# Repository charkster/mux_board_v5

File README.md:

# mux_board_v5
Custom PCB with SAMD21 QT PY controlling TWO ADG1606BRUZ 16 input muxes! This board is 30% smaller than V3 and uses a single 16x2 pin header. There are two firmwares for this board, as the backside input pin numbering does not match the topside numbering. You can select which side you would like to be on-top... the QT PY board is much taller than the ADG1606BRUZ packages, and I plan to have the backside on-top (to aviod any unwanted contact with the boards that I connect to).

Check-out my **PDF** [schematic](https://github.com/charkster/mux_board_v5/blob/main/mux_board_v5.pdf) !!

The SAMD21 QT PY can be programmed with the appropriate file (drag-n-drop) from the uf2_firmware folder. 

**Supported USBTMC commands:**

**MUX1:EN 1** # enable MUX1, a zero will disable the mux

**MUX1:SEL 1** # select S1 input, values 1 through 16 are valid

**MUX1:EN?** # this query returns the state of MUX1

**MUX1:SEL?** # this query returns the presently selected input

***RST** # disables all MUX enables

***IDN?** # returns valid commands and this URL

2x16 2.54mm stacking headers can be found on [Aliexpress](https://www.aliexpress.us/item/2255800630914427.html)

SAMD21 QT PY and ADG1606BRUZ ICs can be found on Digikey/Mouser.

The tinyusb_usbtmc_src files are modifications of https://github.com/hathach/tinyusb source files.

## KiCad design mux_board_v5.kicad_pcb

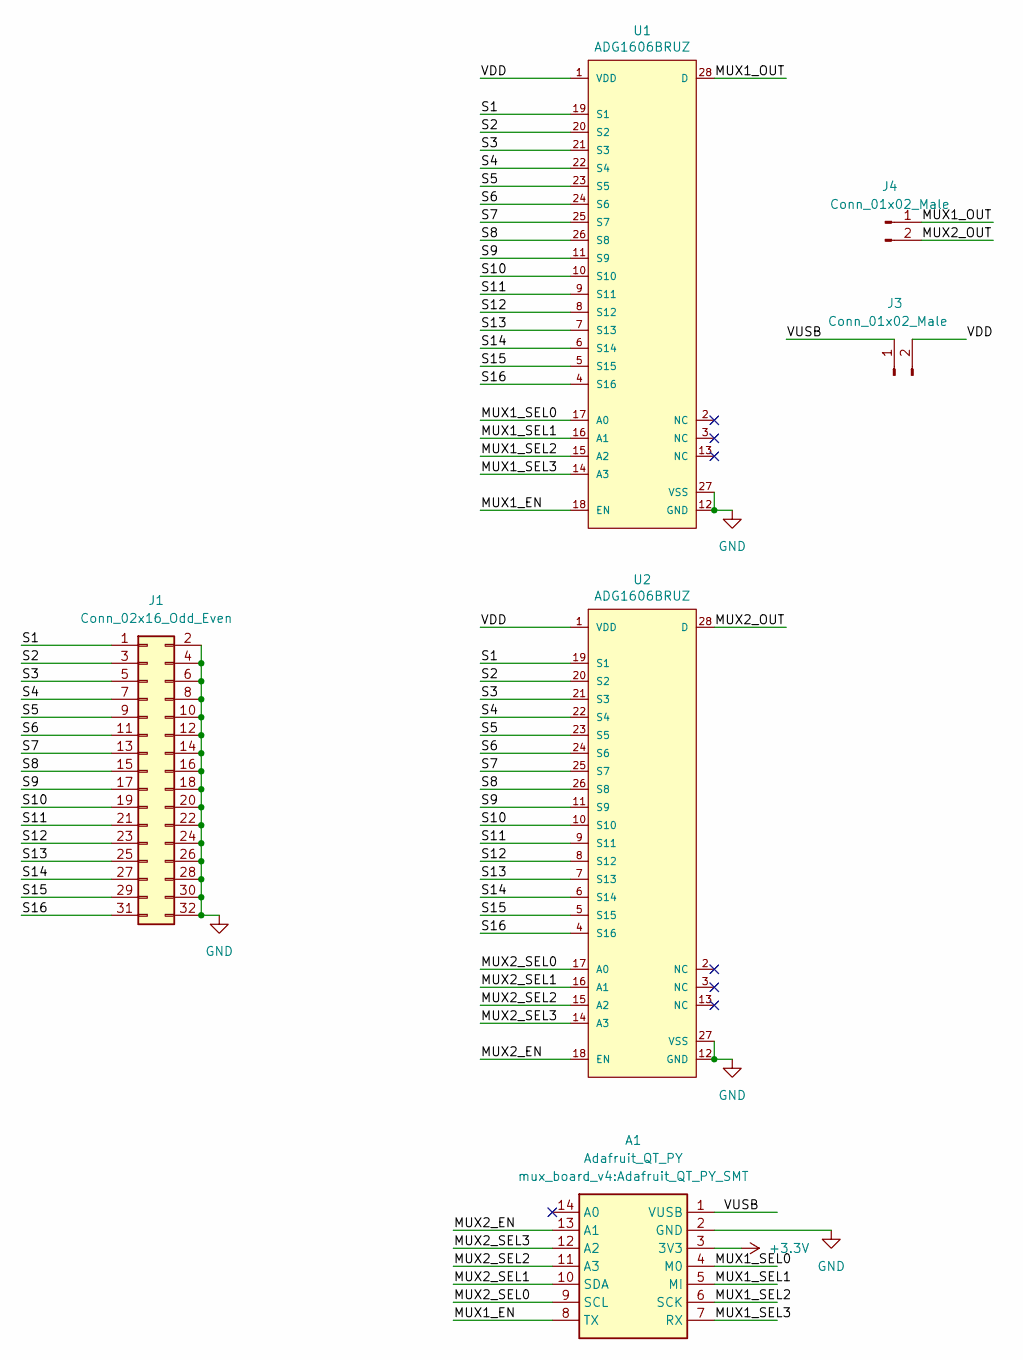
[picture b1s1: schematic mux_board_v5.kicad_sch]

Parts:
A1: Adafruit_QT_PY; Adafruit_QT_PY_SMT
J1: Conn_02x16_Odd_Even; PinHeader_2x16_P2.54mm_Vertical
J3, J4: Conn_01x02_Male; PinHeader_1x02_P2.54mm_Vertical
U1, U2: ADG1606BRUZ; Analog_Devices-RU-28-0-0-IPC_A; mouser part number 584-ADG1606BRUZ; digikey description IC MULTIPLEXER 1 X 16 28TSSOP

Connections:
+3V3: A1.3 (3V3)
/MUX1_EN: A1.8 (TX), U1.18 (EN)
/MUX1_OUT: J4.1, U1.28 (D)
/MUX1_SEL0: A1.4 (M0), U1.17 (A0)
/MUX1_SEL1: A1.5 (MI), U1.16 (A1)
/MUX1_SEL2: A1.6 (SCK), U1.15 (A2)
/MUX1_SEL3: A1.7 (RX), U1.14 (A3)
/MUX2_EN: A1.13 (A1), U2.18 (EN)
/MUX2_OUT: J4.2, U2.28 (D)
/MUX2_SEL0: A1.9 (SCL), U2.17 (A0)
/MUX2_SEL1: A1.10 (SDA), U2.16 (A1)
/MUX2_SEL2: A1.11 (A3), U2.15 (A2)
/MUX2_SEL3: A1.12 (A2), U2.14 (A3)
/S1: J1.1, U1.19 (S1), U2.19 (S1)
/S2: J1.3, U1.20 (S2), U2.20 (S2)
/S3: J1.5, U1.21 (S3), U2.21 (S3)
/S4: J1.7, U1.22 (S4), U2.22 (S4)
/S5: J1.9, U1.23 (S5), U2.23 (S5)
/S6: J1.11, U1.24 (S6), U2.24 (S6)
/S7: J1.13, U1.25 (S7), U2.25 (S7)
/S8: J1.15, U1.26 (S8), U2.26 (S8)
/S9: J1.17, U1.11 (S9), U2.11 (S9)
/S10: J1.19, U1.10 (S10), U2.10 (S10)
/S11: J1.21, U1.9 (S11), U2.9 (S11)
/S12: J1.23, U1.8 (S12), U2.8 (S12)
/S13: J1.25, U1.7 (S13), U2.7 (S13)
/S14: J1.27, U1.6 (S14), U2.6 (S14)
/S15: J1.29, U1.5 (S15), U2.5 (S15)
/S16: J1.31, U1.4 (S16), U2.4 (S16)
/VDD: J3.2, U1.1 (VDD), U2.1 (VDD)
/VUSB: A1.1 (VUSB), J3.1
GND: A1.2 (GND), J1.2, J1.4, J1.6, J1.8, J1.10, J1.12, J1.14, J1.16, J1.18, J1.20, J1.22, J1.24, J1.26, J1.28, J1.30, J1.32, U1.12 (GND), U1.27 (VSS), U2.12 (GND), U2.27 (VSS)

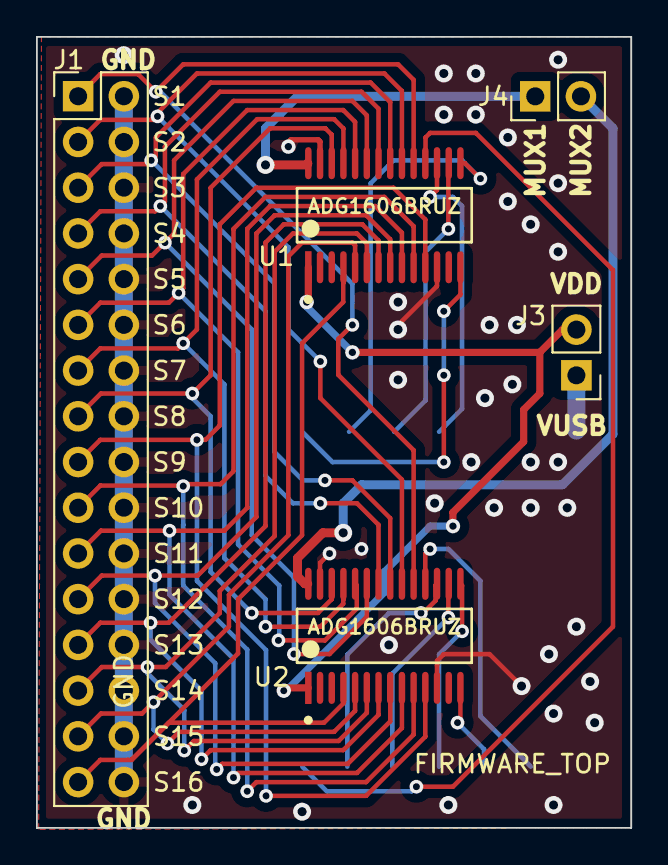
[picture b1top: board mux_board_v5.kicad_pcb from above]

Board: 2 copper layers, 33.0 x 43.9 mm, 6 parts (1 on the bottom side), 31 nets.

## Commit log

2023-04-29 Update README.md
    Fixed programming description

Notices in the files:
mux_board_v5.kicad_pcb:
creativecommons.org/licenses/by/4.0
License: CC BY 4.0
